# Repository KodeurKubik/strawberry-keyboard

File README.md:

# 🍓 strawberry

my own little hackpad to play Celeste!

## Demo?

I'll try getting a demo out after receiving and building the keyboard :D

## Preview:

strawberry 3d case:

and the top case (temporary for now, i'll print multiple tests to make it cool! and paint it :p)

cool PCB!

and the schematic of the PCB

## Folder organisation

Trying to not being messy, here's how it is! (no this is not AI made!)

```
|- assets    # ignore, it's just github assets lol
|- CAD       # 3d models for the case
|- firmware  # firmware for the keyboard
|- PCB       # KiCad PCB and schematics
```

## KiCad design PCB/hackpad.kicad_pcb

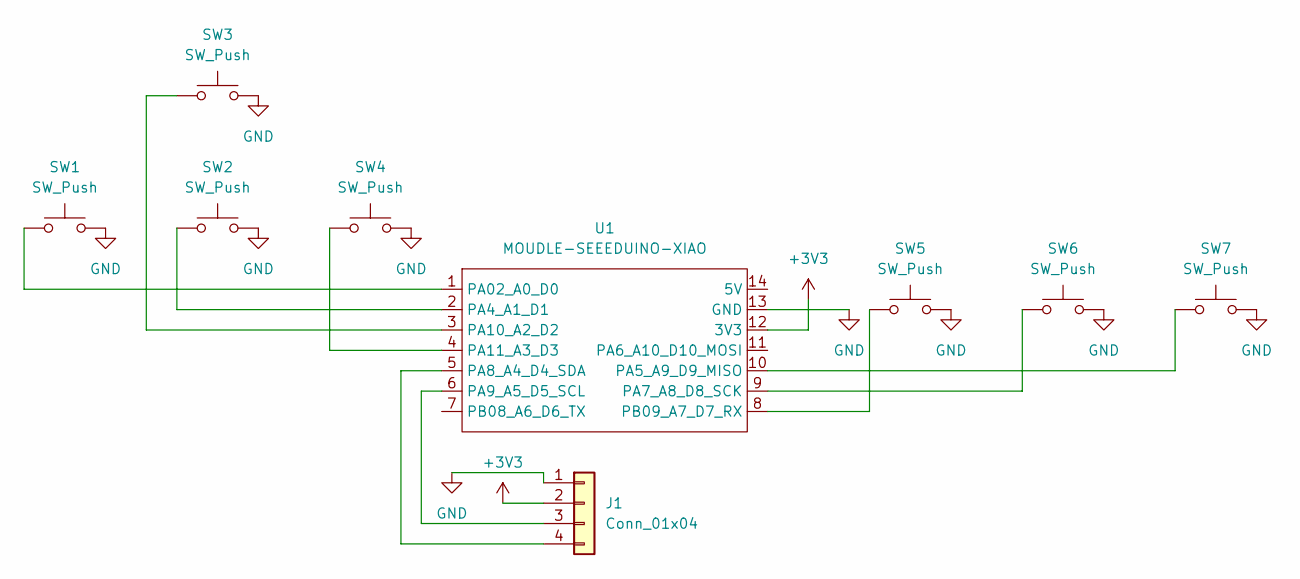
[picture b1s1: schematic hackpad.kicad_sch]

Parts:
J1: Conn_01x04; PinHeader_1x04_P2.54mm_Vertical
SW1, SW2, SW3, SW4, SW5, SW6, SW7: SW_Push; SW_Cherry_MX_1.00u_PCB
U1: MOUDLE-SEEEDUINO-XIAO; XIAO-Generic-Hybrid-14P-2.54-21X17.8MM

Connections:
+3V3: J1.2, U1.12 (3V3)
GND: J1.1, SW1.2, SW2.2, SW3.2, SW4.2, SW5.2, SW6.2, SW7.2, U1.13 (GND)
unnamed: J1.3, U1.6 (PA9_A5_D5_SCL)
unnamed: J1.4, U1.5 (PA8_A4_D4_SDA)
unnamed: SW1.1, U1.1 (PA02_A0_D0)
unnamed: SW2.1, U1.2 (PA4_A1_D1)
unnamed: SW7.1, U1.10 (PA5_A9_D9_MISO)
unnamed: SW6.1, U1.9 (PA7_A8_D8_SCK)
unnamed: SW3.1, U1.3 (PA10_A2_D2)
unnamed: SW4.1, U1.4 (PA11_A3_D3)
unnamed: SW5.1, U1.8 (PB09_A7_D7_RX)

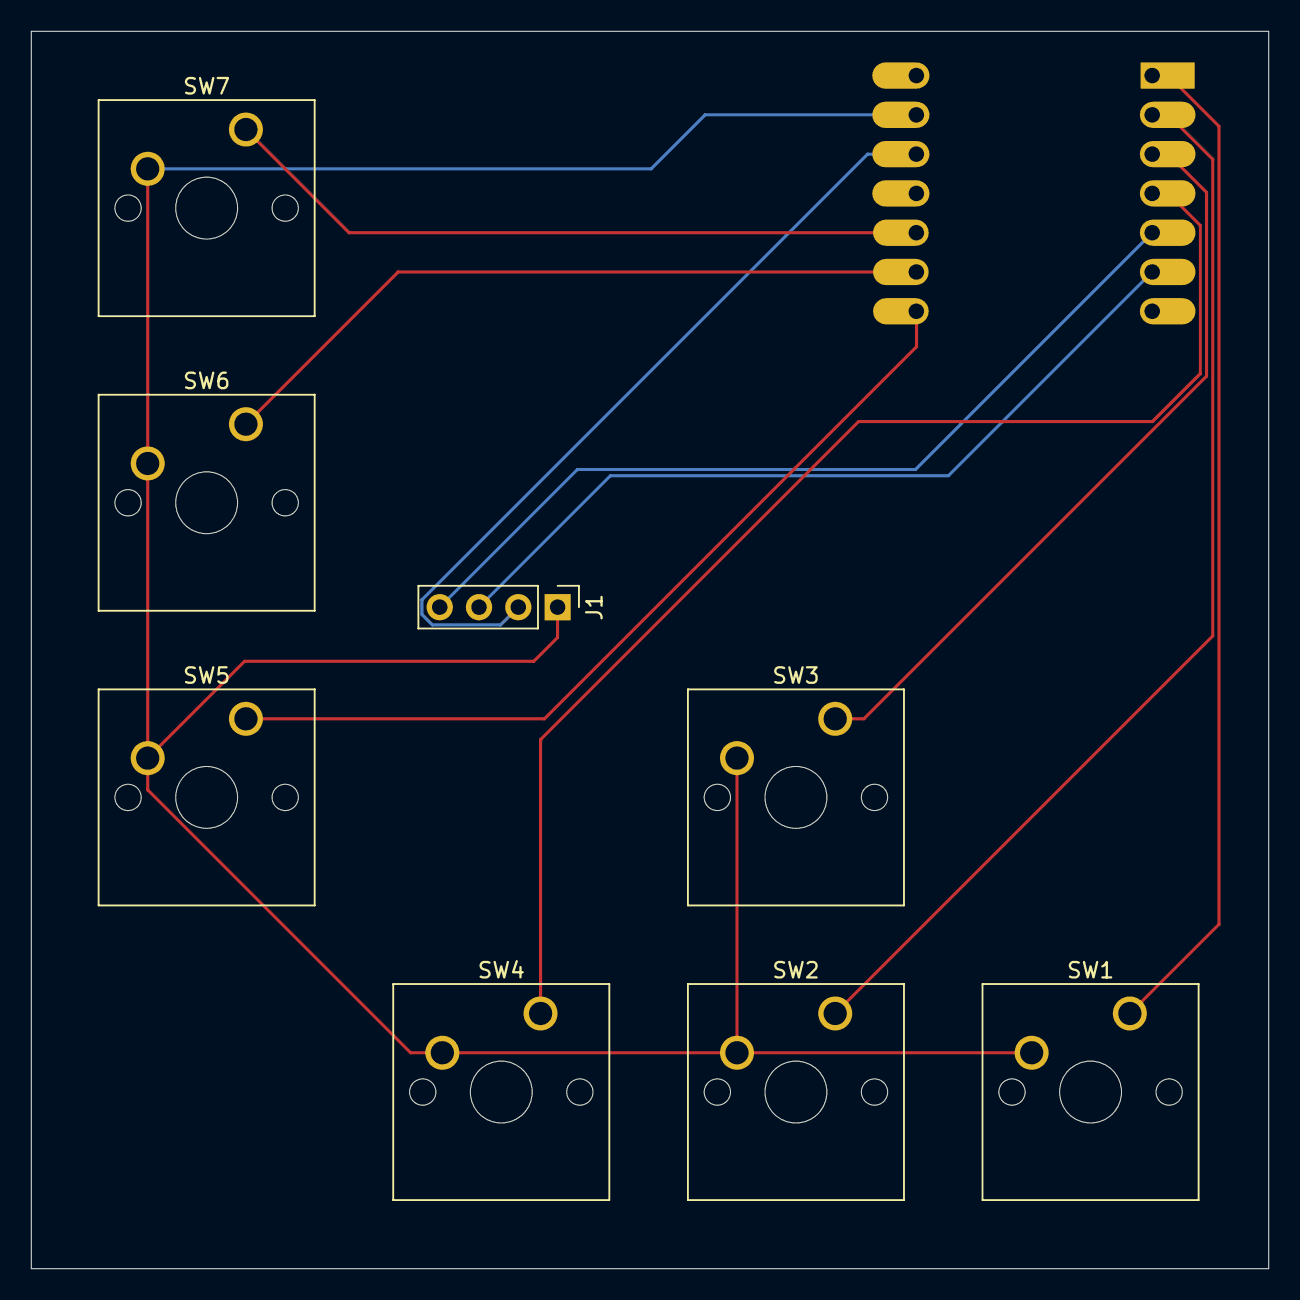
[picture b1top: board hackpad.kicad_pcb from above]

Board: 2 copper layers, 80.0 x 80.0 mm, 9 parts (1 on the bottom side), 11 nets.
